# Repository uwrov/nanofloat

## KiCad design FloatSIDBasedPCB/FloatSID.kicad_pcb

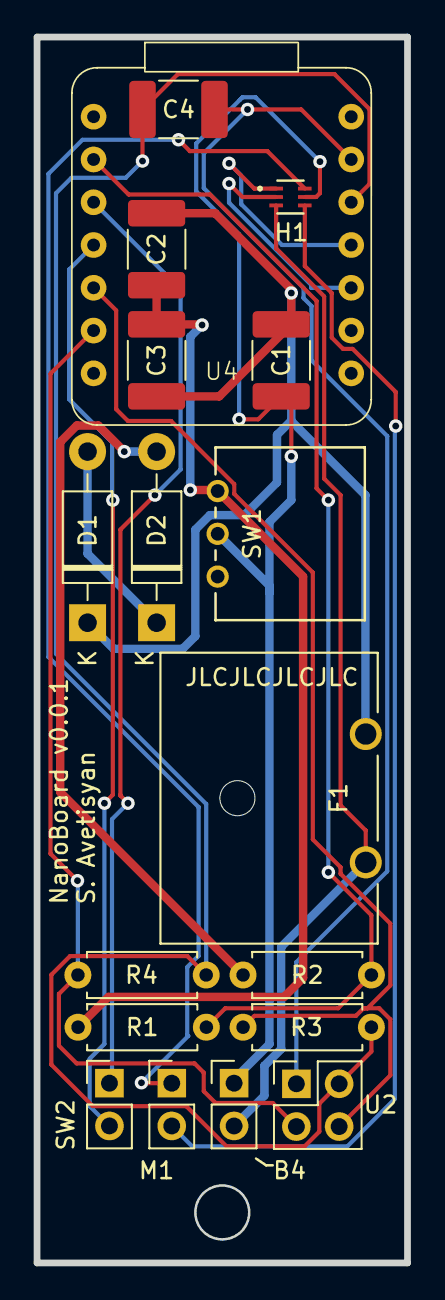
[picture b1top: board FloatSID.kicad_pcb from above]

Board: 2 copper layers, 22.0 x 72.8 mm, 18 parts (0 on the bottom side), 14 nets.

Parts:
B4: 1.5V; PinHeader_1x02_P2.54mm_Vertical
C1, C2, C3, C4: C_Small; C_1812_4532Metric_Pad1.57x3.40mm_HandSolder
D1, D2: Rectifier Diode; D_DO-41_SOD81_P10.16mm_Horizontal
F1: 2A Fuse; FUSE_01530007Z
H1: DRV8220DRLR
M1: Motor_DC; PinHeader_1x02_P2.54mm_Vertical
R1, R2: 220kOhm; R_Axial_DIN0207_L6.3mm_D2.5mm_P7.62mm_Horizontal
R3, R4: 10kOhm; R_Axial_DIN0207_L6.3mm_D2.5mm_P7.62mm_Horizontal
SW1: SW; SW_09.10290.01_EAO
SW2: Limit Switch; PinHeader_1x02_P2.54mm_Vertical
U2: MS583730BA01-50; PinHeader_2x02_P2.54mm_Vertical
U4: XiaoESP32C3; XIAO_ESP32C3_THT

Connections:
unnamed: B4.1 (+), C1.1, H1.5, SW1.1 (A)
unnamed: B4.2 (-), F1.2, H1.3
unnamed: D1.2 (A), D2.1 (K)
unnamed: C1.2, C2.2, C3.1, D1.1 (K), F1.1
unnamed: D2.2 (A), R2.1
unnamed: H1.1, U4.10 (D9)
unnamed: H1.6, M1.1 (+)
unnamed: H1.4, M1.2 (-)
unnamed: C2.1, C3.2, R1.1, SW1.2 (B)
unnamed: C4.2, U2.1 (GND), U4.GND
unnamed: R4.1, U2.3 (SCL), U4.5 (D4_SDA)
unnamed: R3.2, U2.4 (SDA), U4.4 (D3)
unnamed: C4.1, R3.1, R4.2, U2.2 (VDD), U4.3V3
unnamed: R1.2, R2.2, U4.1 (D0)
